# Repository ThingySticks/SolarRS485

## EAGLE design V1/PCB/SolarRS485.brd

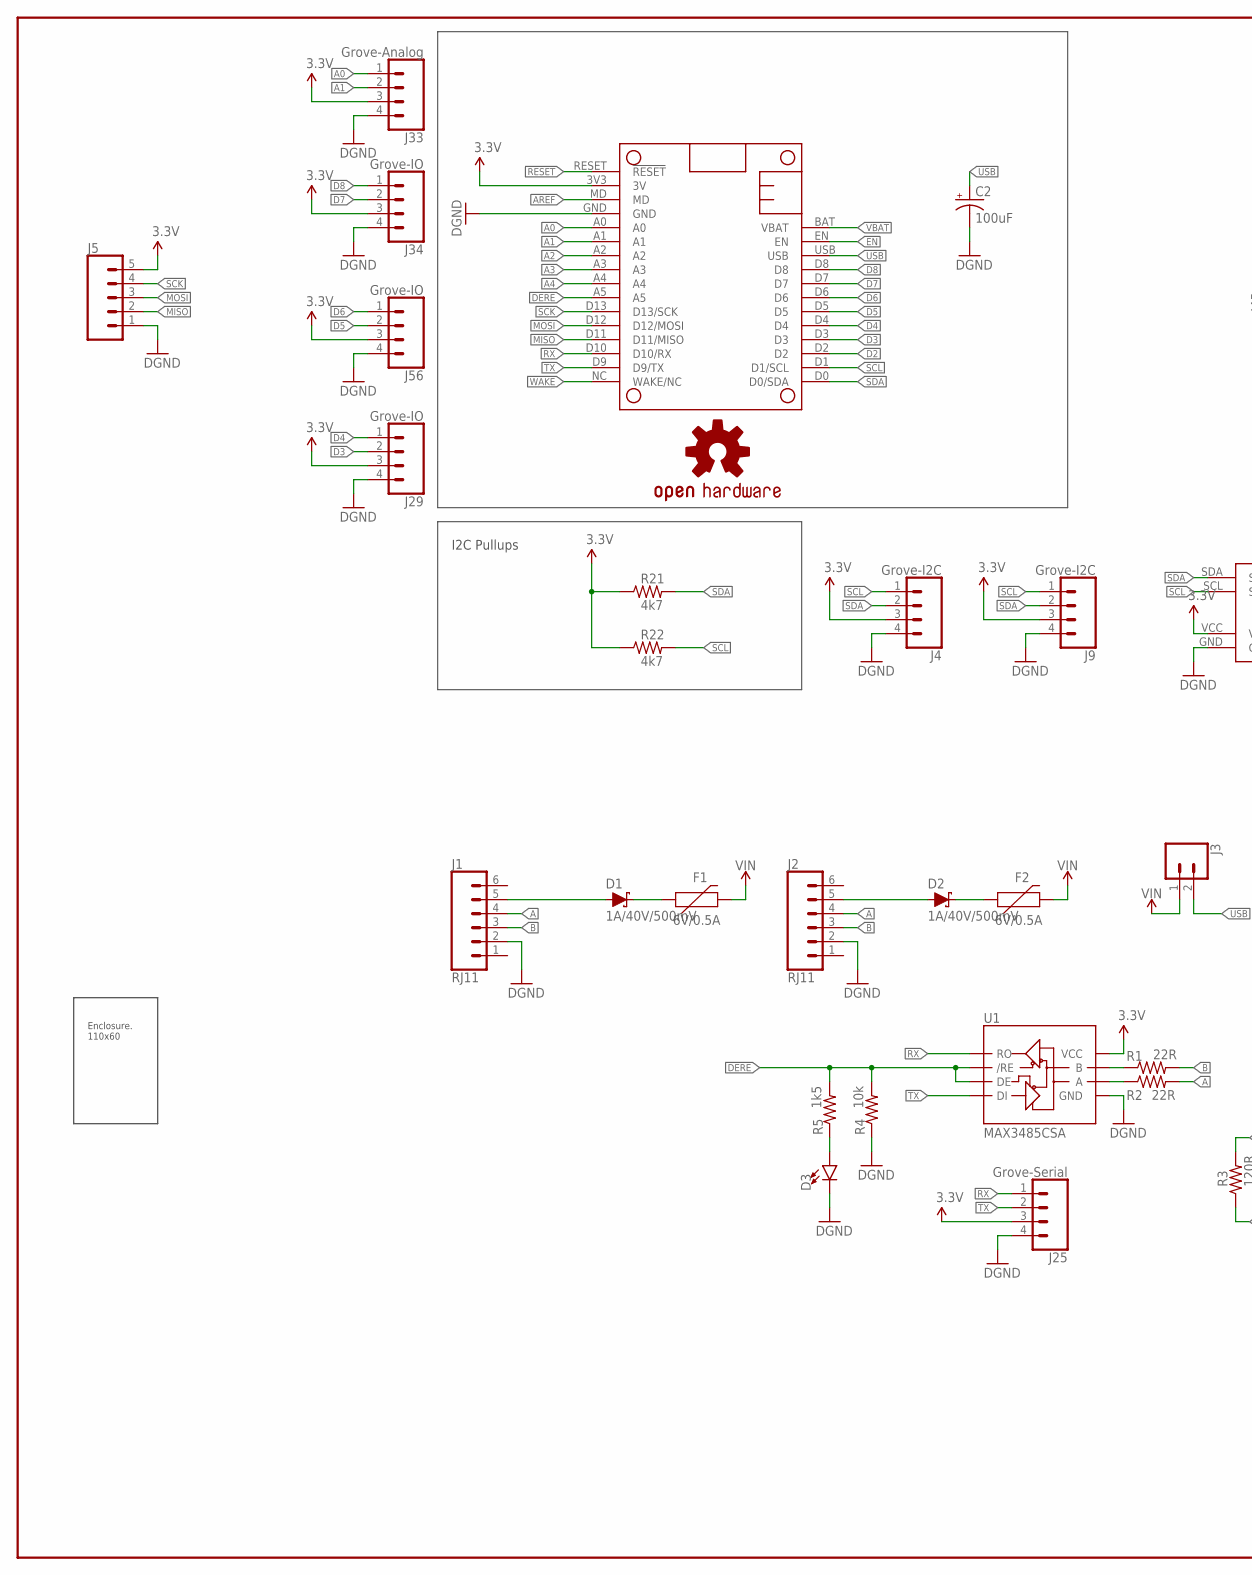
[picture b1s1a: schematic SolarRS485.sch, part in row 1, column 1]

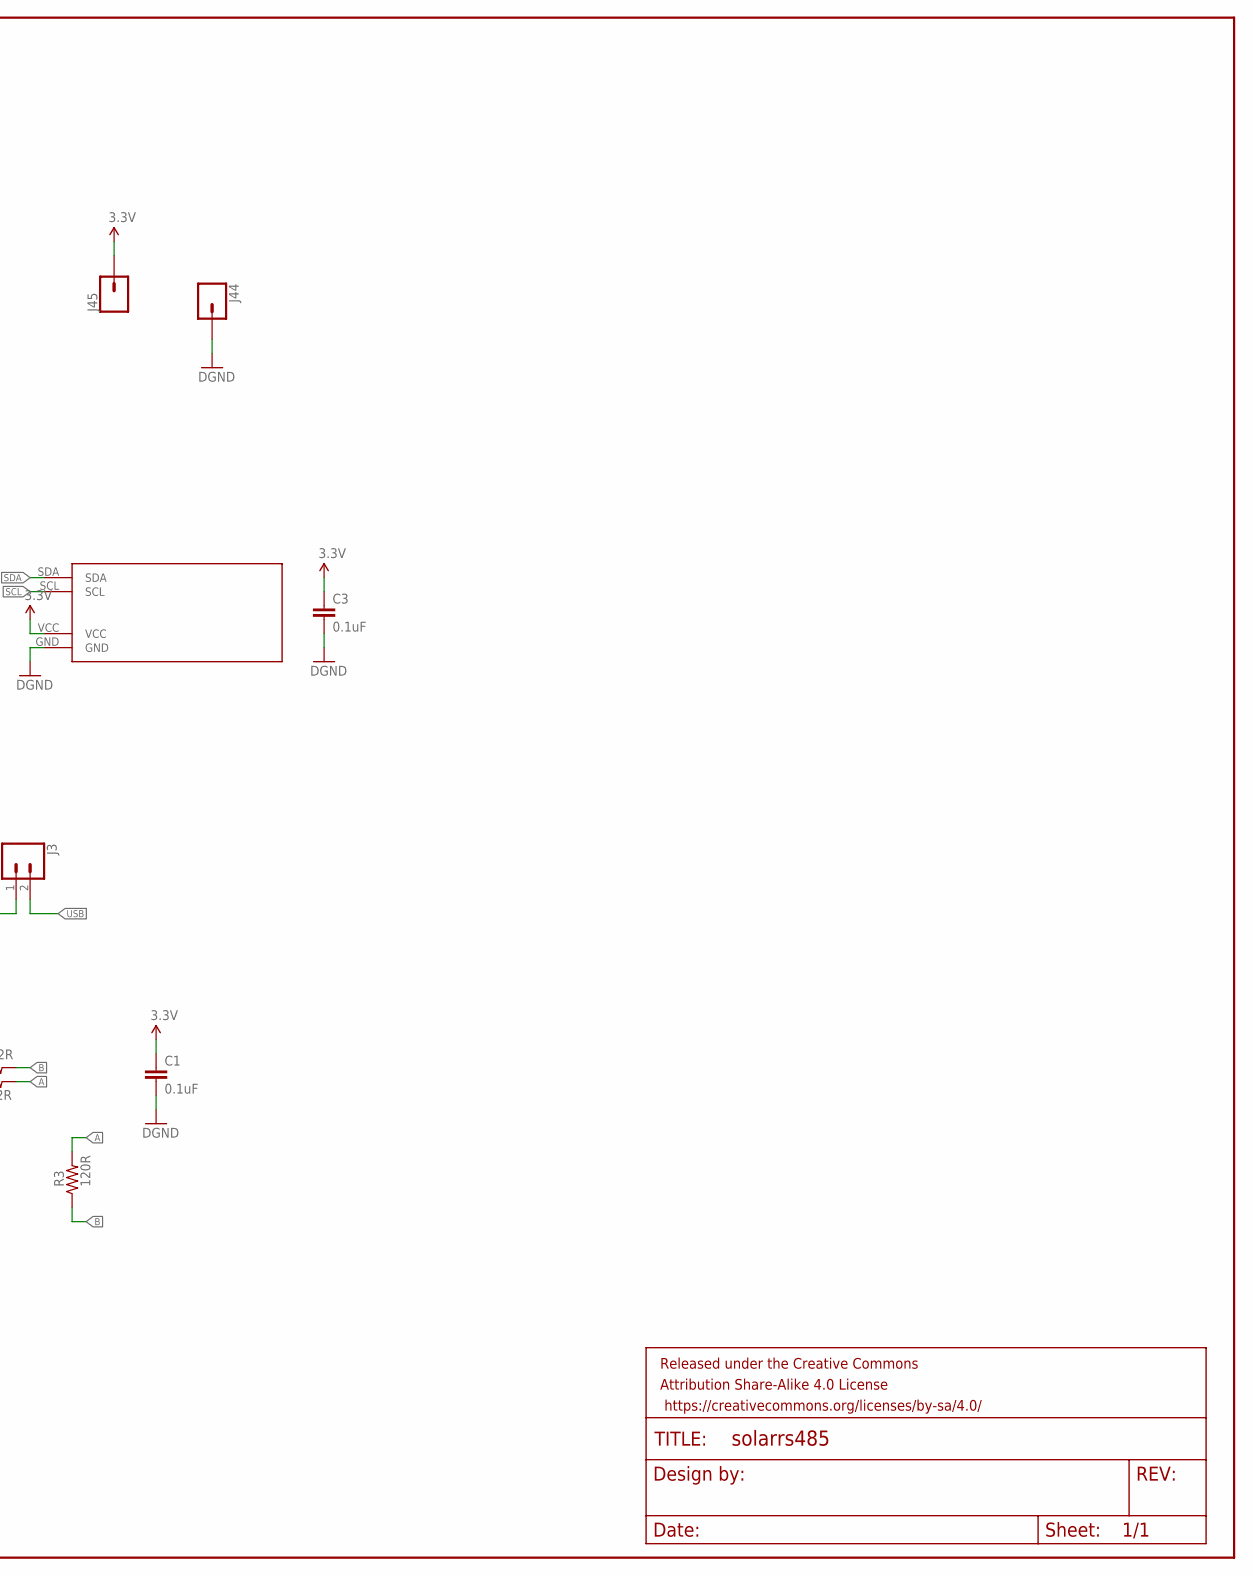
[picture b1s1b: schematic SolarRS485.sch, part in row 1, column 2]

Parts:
C1, C3: 0.1uF; 0805
C2: 100uF; CPOL-RADIAL-2.5MM-6.5MM
D1, D2: 1A/40V/500mV; SMA-DIODE
D3: LEDLED-1206-BOTTOM-2.0MM-BLUE; LED-1206-BOTTOM-2.0MM
F1, F2: 6V/0.5A; 1206
FRAME2: FRAME-LEDGER; CREATIVE_COMMONS
J1, J2: RJ11; RJ11-6
J3: CONN_02; 1X02
J4, J9: Grove-I2C; JST-4-PH-GROVE
J5: CONN_05; 1X05
J25: Grove-Serial; JST-4-PH-GROVE
J29, J34, J56: Grove-IO; JST-4-PH-GROVE
J33: Grove-Analog; JST-4-PH-GROVE
J44, J45: CONN_01PTH_NO_SILK_YES_STOP; 1X01_NO_SILK
LOGO1: OSHW-LOGOM; OSHW-LOGO-M
MS1: XENONA; XENON_BREAKOUT_A
R1, R2: 22R; 0805
R3: 120R; 0805
R4: 10k; 0805
R5: 1k5; 0805
R21, R22: 4k7; 0805
U1: MAX3485CSA; SO08
U$1: CAMDENBOSS-ENCLOSURE-110X60BOTH-EXTENDED-WIDE; CAMDENBOSS_ENCLOSURE_110X60_WIDE_EXTENDED
U$2: DISPLAY0.96_INCH_DISPLAY; I2C_DISPLAY_0.96_INCH

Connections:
3.3V: C1.1, C3.1, J4.3, J5.5, J9.3, J25.3, J29.3, J33.3, J34.3, J45.1, J56.3, MS1.3V3 (3V), R21.1, R22.1, U1.8 (VCC), U$2.VCC
A: J1.4, J2.4, R2.2, R3.2
A0: J33.1, MS1.A0
A1: J33.2, MS1.A1
A2: MS1.A2
A3: MS1.A3
A4: MS1.A4
AREF: MS1.MD
B: J1.3, J2.3, R1.2, R3.1
D2: MS1.D2
D3: J29.2, MS1.D3
D4: J29.1, MS1.D4
D5: J56.2, MS1.D5
D6: J56.1, MS1.D6
D7: J34.2, MS1.D7
D8: J34.1, MS1.D8
DERE: MS1.A5, R4.2, R5.2, U1.2 (/RE), U1.3 (DE)
EN: MS1.EN
GND: C1.2, C2.2 (-), C3.2, D3.C, J1.2, J2.2, J4.4, J5.1, J9.4, J25.4, J29.4, J33.4, J34.4, J44.1, J56.4, MS1.GND, R4.1, U1.5 (GND), U$2.GND
MISO: J5.2, MS1.D11 (D11/MISO)
MOSI: J5.3, MS1.D12 (D12/MOSI)
unnamed: D2.A, J2.5
unnamed: D1.A, J1.5
unnamed: D2.C, F2.1
unnamed: D1.C, F1.1
unnamed: R1.1, U1.7 (B)
unnamed: R2.1, U1.6 (A)
unnamed: D3.A, R5.1
RESET: MS1.RESET (!RESET)
RX: J25.1, MS1.D10 (D10/RX), U1.1 (RO)
SCK: J5.4, MS1.D13 (D13/SCK)
SCL: J4.1, J9.1, MS1.D1 (D1/SCL), R22.2, U$2.SCL
SDA: J4.2, J9.2, MS1.D0 (D0/SDA), R21.2, U$2.SDA
TX: J25.2, MS1.D9 (D9/TX), U1.4 (DI)
USB: C2.1 (+), J3.2, MS1.USB
VBAT: MS1.BAT (VBAT)
VIN: F1.2, F2.2, J3.1
WAKE: MS1.NC (WAKE/NC)

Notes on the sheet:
I2C Pullups

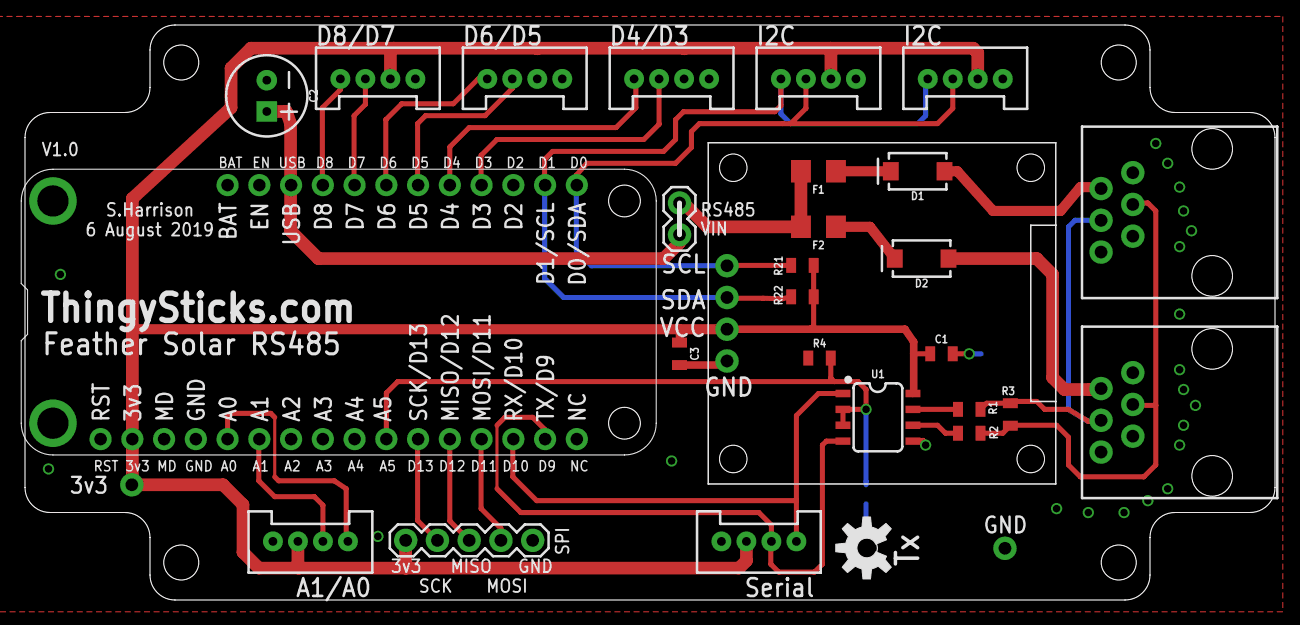
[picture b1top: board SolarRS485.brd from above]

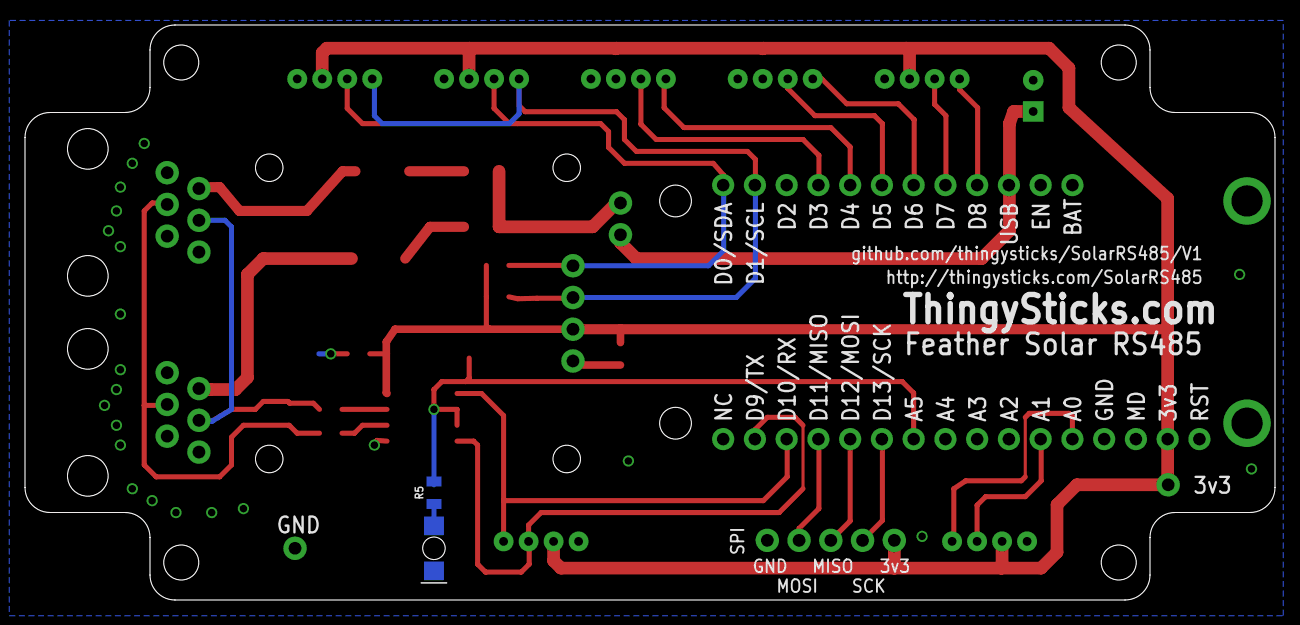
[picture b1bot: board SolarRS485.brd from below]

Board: 2 copper layers, 100.0 x 46.0 mm, 34 parts (2 on the bottom side), 29 nets.

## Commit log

2020-01-11 Version 2. Switched to RJ45's to make connecting easier.
    Fixed A/B of 485 the wrong way around
    Added 5V regulator option to allow for higher bus voltages for other usages.
2020-01-11 Adding V1 for reference.
    Do Not Use - A/B swapped!
2020-01-12 Updated version number
    Added some documentation / datasheets.
    Added gitignore

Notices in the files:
parts and their libraries:
SparkFun-Aesthetics: Licensing: Creative Commons ShareAlike 4.0 International - https://creativecommons.org/licenses/by-sa/4.0
SparkFun-Aesthetics: Released under the Creative Commons Attribution Share-Alike 4.0 License
SparkFun-Aesthetics: https://creativecommons.org/licenses/by-sa/4.0
